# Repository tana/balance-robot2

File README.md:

# Self-balancing robot using LQR control, written in Rust

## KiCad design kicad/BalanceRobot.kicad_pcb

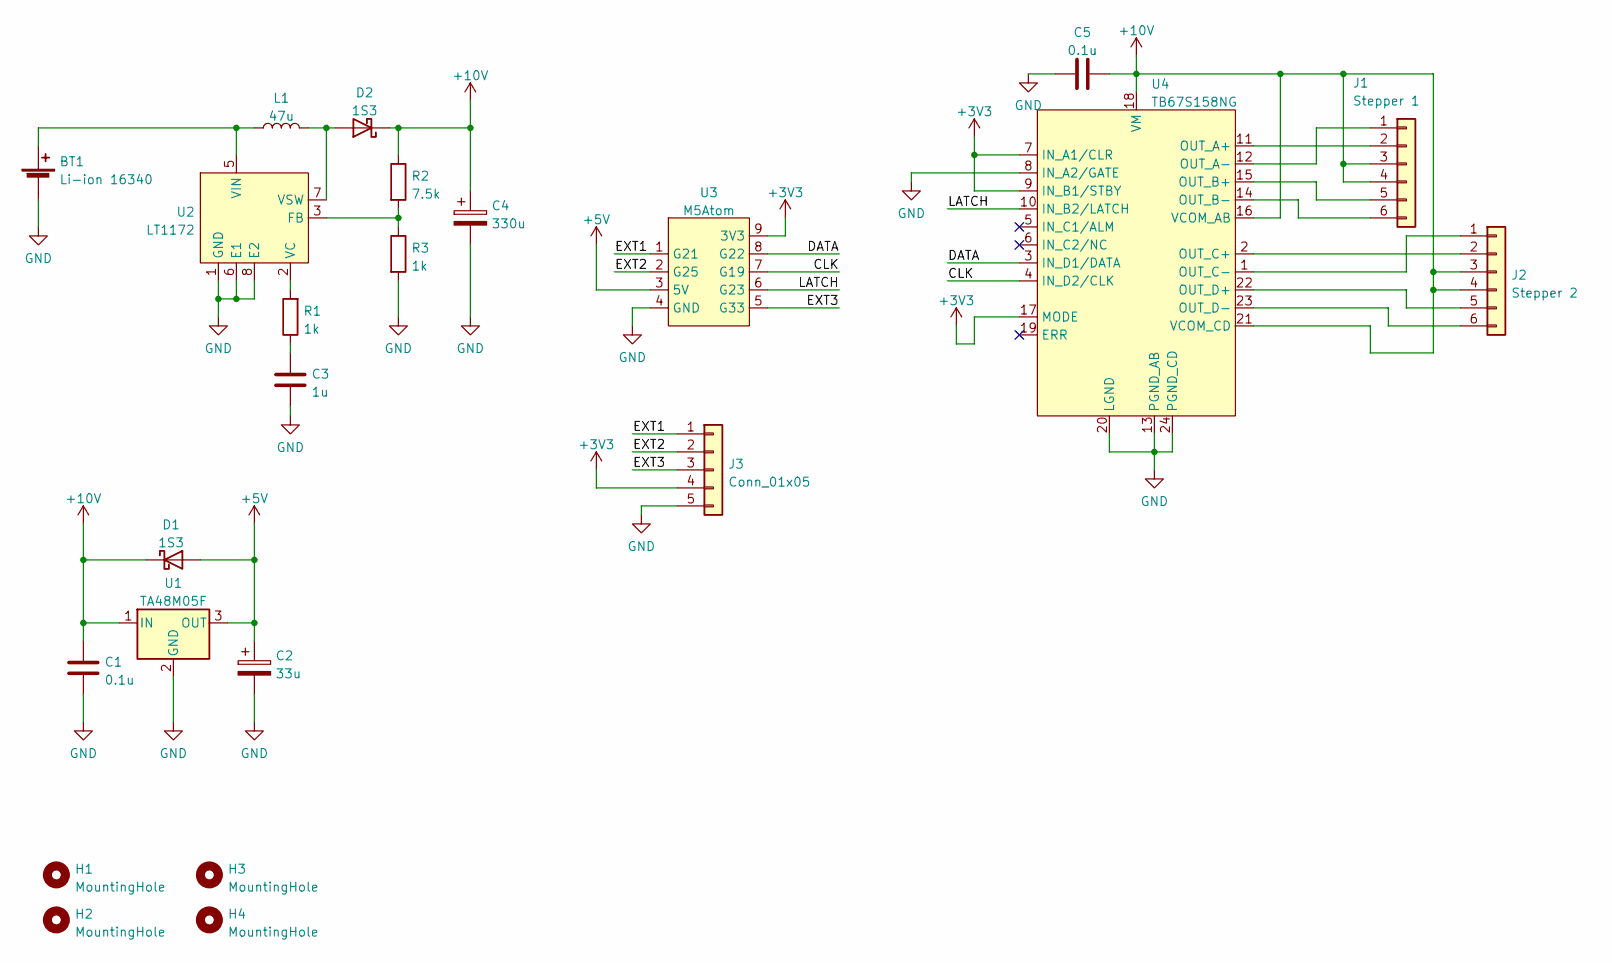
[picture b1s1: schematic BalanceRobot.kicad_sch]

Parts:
BT1: Li-ion 16340; Takachi_CR123A-PC
C1, C5: 0.1u; C_Disc_D3.0mm_W1.6mm_P2.50mm
C2: 33u; CP_Radial_D5.0mm_P2.50mm
C3: 1u; C_Disc_D3.0mm_W1.6mm_P2.50mm
C4: 330u; CP_Radial_D8.0mm_P5.00mm
D1, D2: 1S3; D_DO-34_SOD68_P7.62mm_Horizontal
H1, H2, H3, H4: MountingHole; MountingHole_3.2mm_M3
J1: Stepper 1; PinHeader_1x06_P2.54mm_Vertical
J2: Stepper 2; PinHeader_1x06_P2.54mm_Vertical
J3: Conn_01x05; PinHeader_1x05_P2.54mm_Vertical
L1: 47u; L_Radial_D10.5mm_P5.00mm_Abacron_AISR-01
R1, R3: 1k; R_Axial_DIN0207_L6.3mm_D2.5mm_P7.62mm_Horizontal
R2: 7.5k; R_Axial_DIN0207_L6.3mm_D2.5mm_P7.62mm_Horizontal
U1: TA48M05F; TO-251-3_Vertical
U2: LT1172; DIP-8_W7.62mm
U3: M5Atom
U4: TB67S158NG; SDIP24_300mil

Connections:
+3V3: J3.4, U3.9 (3V3), U4.7 (IN_A1/CLR), U4.9 (IN_B1/STBY), U4.17 (MODE)
+5V: C2.1, D1.2 (A), U1.3 (OUT), U3.3 (5V)
+10V: C1.1, C4.1, C5.2, D1.1 (K), D2.1 (K), J1.3, J1.4, J2.3, J2.4, R2.1, U1.1 (IN), U4.16 (VCOM_AB), U4.18 (VM), U4.21 (VCOM_CD)
/CLK: U3.7 (G19), U4.4 (IN_D2/CLK)
/DATA: U3.8 (G22), U4.3 (IN_D1/DATA)
/EXT1: J3.1, U3.1 (G21)
/EXT2: J3.2, U3.2 (G25)
/EXT3: J3.3, U3.5 (G33)
/LATCH: U3.6 (G23), U4.10 (IN_B2/LATCH)
GND: BT1.2 (-), C1.2, C2.2, C3.2, C4.2, C5.1, J3.5, R3.2, U1.2 (GND), U2.1 (GND), U2.6 (E1), U2.8 (E2), U3.4 (GND), U4.8 (IN_A2/GATE), U4.13 (PGND_AB), U4.20 (LGND), U4.24 (PGND_CD)
unnamed: BT1.1 (+), L1.1, U2.5 (VIN)
unnamed: C3.1, R1.1
unnamed: D2.2 (A), L1.2, U2.7 (VSW)
unnamed: J1.1, U4.12 (OUT_A-)
unnamed: J1.2, U4.11 (OUT_A+)
unnamed: J1.5, U4.15 (OUT_B+)
unnamed: J1.6, U4.14 (OUT_B-)
unnamed: J2.1, U4.1 (OUT_C-)
unnamed: J2.2, U4.2 (OUT_C+)
unnamed: J2.5, U4.22 (OUT_D+)
unnamed: J2.6, U4.23 (OUT_D-)
unnamed: R1.2, U2.2 (VC)
unnamed: R2.2, R3.1, U2.3 (FB)

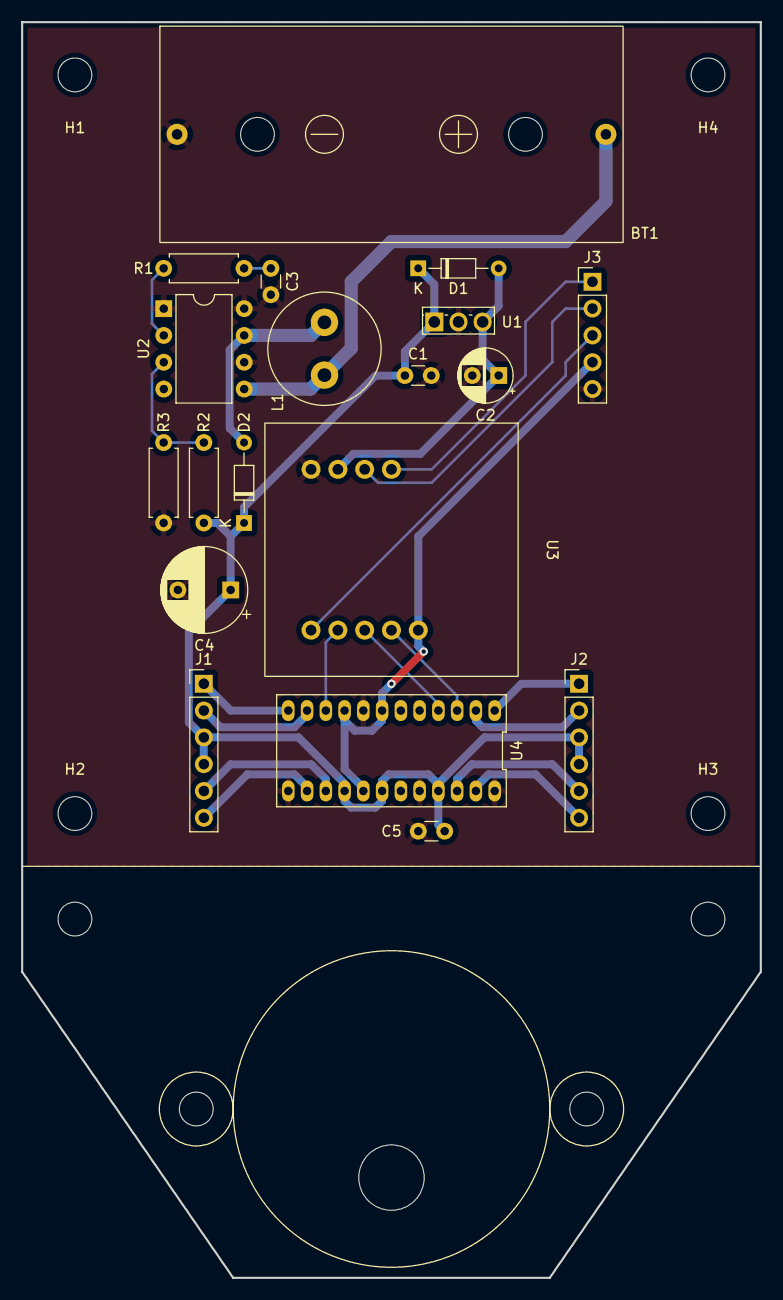
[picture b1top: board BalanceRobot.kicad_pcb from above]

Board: 2 copper layers, 70.0 x 119.0 mm, 23 parts (0 on the bottom side), 23 nets.

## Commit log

2022-12-20 Stepper driver
2022-12-21 Add KiCad files
2022-12-22 Fix bit order of steppers
2022-12-22 Update schematic to reflect actual values
2022-12-29 Constant speed pulse generation for steppers
2022-12-29 Button for toggling motor on/off
2022-12-29 Implement control but unsuccessful
2022-12-30 Use filtered angular velocity
2022-12-30 Toggle GPIO33 for debug
2023-01-03 (WIP) microstepping Updated ESP-IDF to v5.0
2023-01-03 Implement microstepping
2023-01-03 Change gain and some fixes
2023-01-03 Revert "Implement microstepping"
    This reverts commit 56e40cff70498bef762ddbb85099dc7a059d9d55.
2023-01-03 Revert "(WIP) microstepping"
    This reverts commit 665b255de0fa59d8b344f2f43de44f53dec14450.
2023-01-03 Include custom KiCad libraries
2023-01-04 Add readme, license, etc.
2023-01-09 Implement OSC receiver (actual control is not yet)
2023-01-09 Add mDNS .local advertising
2023-01-09 Implement turn. A bit unstable
2023-01-09 Fix turn limit calculation
2023-01-09 Fix crash on Wi-Fi connect/disconnect
2023-01-09 Add forward/back speed control
2023-01-09 Add TouchOSC-based control interface
